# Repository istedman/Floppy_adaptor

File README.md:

# Floppy_adaptor V2.5
Converts PC floppy drive interface to Amiga/Shugart bus interface. Now also supports the Atari ST/TT. Only supports Double Density (DD) disks but works with an HD drive in DD mode.

The native files in EagleCAD format are included. The Zip file contains the Gerber data.
# 2021 Update.
I'm discontinuing sales of all Amiga related projects. Reduced order volumes and extra issues with order post Brexit have not made it viable to continue.
All information, including BOMs, Gerbers and notes are now in the repository, if you want to build your own.

The design supports use as an external drive, see the file External_drive_wiring_V2.png for details.

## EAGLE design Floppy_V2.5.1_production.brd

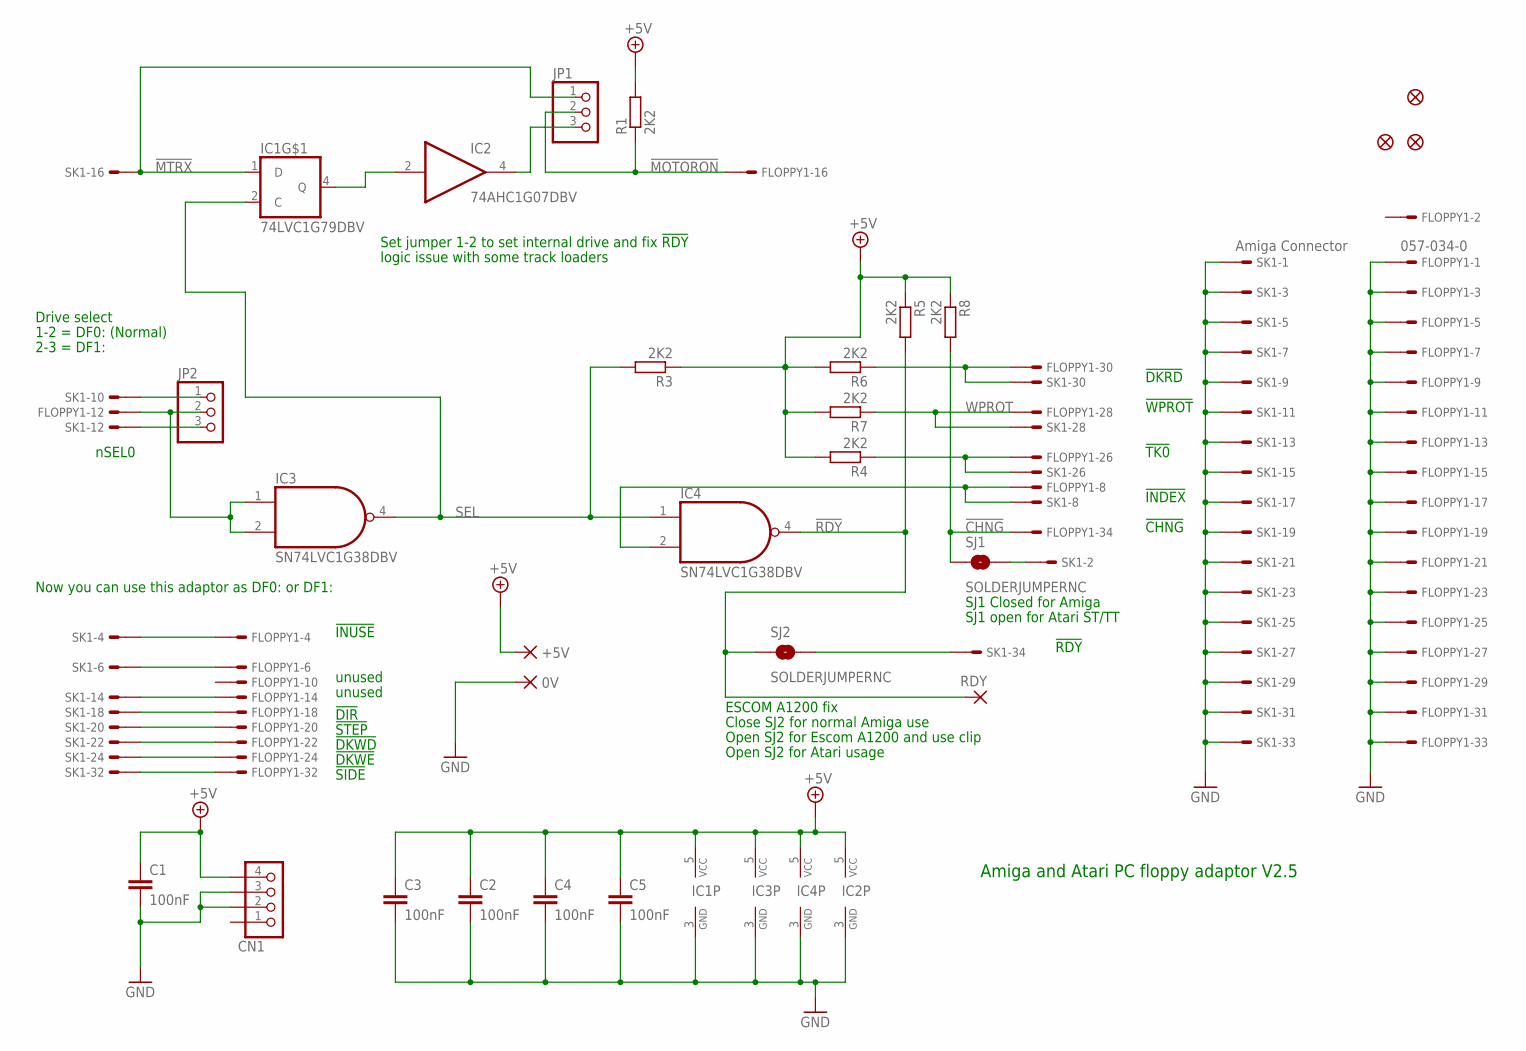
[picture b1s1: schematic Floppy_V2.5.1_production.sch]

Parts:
0V: PAD-0360-S; 0360-S
+5V: PAD-0360-S; 0360-S
C1, C2, C3, C4, C5: 100nF; C0603
CN1: IANS_FLOPPY_RA; IANS_FLOPPYPOWER__RA
FLOPPY1: 057-034-0
IC1: 74LVC1G79DBV; SOT23-5
IC2: 74AHC1G07DBV; SOT23-5
IC3, IC4: SN74LVC1G38DBV; SOT23-5
JP1, JP2: PINHD-1X3; 1X03
JP3, JP4, JP5: FIDUCIAL1X2; FIDUCIAL-1X2
R1, R3, R4, R5, R6, R7, R8: 2K2; R0603
RDY: 2,15/1,0
SJ1, SJ2: SOLDERJUMPERNC; SJ_2S
SK1: Amiga Connector; 057-034-1

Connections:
!CHNG: FLOPPY1.34, R8.2, SJ1.1
!MOTORON: FLOPPY1.16, JP1.2, R1.1
!MTRX: IC1.1 (D), JP1.1, SK1.16
!RDY: IC4.4 (O), R5.2, RDY.1, SJ2.1
+5V: +5V.P$1, C1.1, C2.1, C3.1, C4.1, C5.1, CN1.4 (+5V), IC1.5 (VCC), IC2.5 (VCC), IC3.5 (VCC), IC4.5 (VCC), R1.2, R3.1, R4.2, R5.1, R6.2, R7.2, R8.1
GND: 0V.P$1, C1.2, C2.2, C3.2, C4.2, C5.2, CN1.2 (GND), CN1.3 (GND), FLOPPY1.1, FLOPPY1.3, FLOPPY1.5, FLOPPY1.7, FLOPPY1.9, FLOPPY1.11, FLOPPY1.13, FLOPPY1.15, FLOPPY1.17, FLOPPY1.19, FLOPPY1.21, FLOPPY1.23, FLOPPY1.25, FLOPPY1.27, FLOPPY1.29, FLOPPY1.31, FLOPPY1.33, IC1.3 (GND), IC2.3 (GND), IC3.3 (GND), IC4.3 (GND), SK1.1, SK1.3, SK1.5, SK1.7, SK1.9, SK1.11, SK1.13, SK1.15, SK1.17, SK1.19, SK1.21, SK1.23, SK1.25, SK1.27, SK1.29, SK1.31, SK1.33
unnamed: IC1.4 (Q), IC2.2 (I)
unnamed: IC2.4 (O), JP1.3
unnamed: FLOPPY1.8, IC4.2 (I1), SK1.8
unnamed: FLOPPY1.26, R4.1, SK1.26
unnamed: FLOPPY1.14, SK1.14
unnamed: FLOPPY1.30, R6.1, SK1.30
unnamed: JP2.1, SK1.10
unnamed: FLOPPY1.12, IC3.1 (I0), IC3.2 (I1), JP2.2
unnamed: JP2.3, SK1.12
unnamed: FLOPPY1.18, SK1.18
unnamed: FLOPPY1.20, SK1.20
unnamed: FLOPPY1.22, SK1.22
unnamed: FLOPPY1.24, SK1.24
unnamed: FLOPPY1.32, SK1.32
unnamed: FLOPPY1.4, SK1.4
unnamed: FLOPPY1.6, SK1.6
unnamed: SJ1.2, SK1.2
unnamed: SJ2.2, SK1.34
SEL: IC1.2 (C), IC3.4 (O), IC4.1 (I0), R3.2
WPROT: FLOPPY1.28, R7.1, SK1.28

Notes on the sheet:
!DKRD
!WPROT
!TK0
!INDEX
nSEL0
!CHNG
!RDY
ESCOM A1200 fix
Close SJ2 for normal Amiga use
Open SJ2 for Escom A1200 and use clip
!INUSE
unused
Amiga and Atari PC floppy adaptor V2.5
Drive select
1-2 = DF0: (Normal)
2-3 = DF1:
Now you can use this adaptor as DF0: or DF1:
Set jumper 1-2 to set internal drive and fix !RDY
logic issue with some track loaders
!DIR
!STEP
!DKWD
!DKWE
!SIDE
SJ1 Closed for Amiga
SJ1 open for Atari ST/TT
Open SJ2 for Atari usage

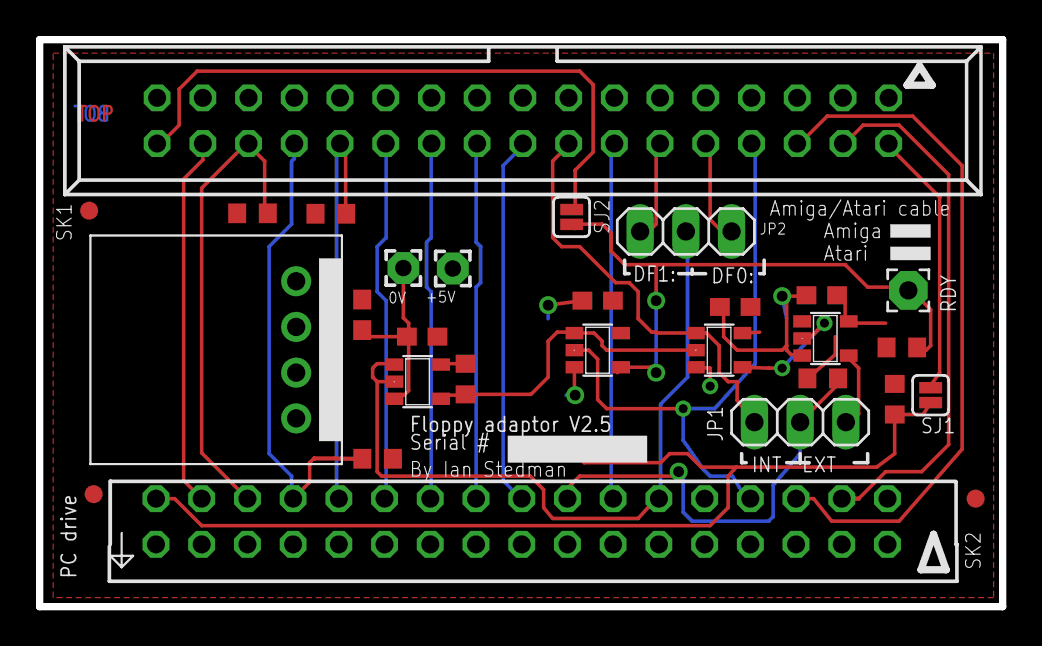
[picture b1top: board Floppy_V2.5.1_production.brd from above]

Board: 2 copper layers, 53.5 x 31.5 mm, 29 parts (0 on the bottom side), 26 nets.

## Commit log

2021-09-12 Add files via upload
    Gerber images used for the last production batch.
2021-09-13 Add files via upload
    Export from Excel of the most recent BOM from Excel used for the last build.
2021-09-14 Add files via upload
    The most recent bill of materials, exported from the Excel master.
